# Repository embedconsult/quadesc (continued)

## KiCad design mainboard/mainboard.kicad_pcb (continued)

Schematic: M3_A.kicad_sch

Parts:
C40, C95: 1nF; C_0201_0603Metric
C41: 10uF; C_1206_3216Metric
C42: 4.7nF; C_0402_1005Metric
C43: 10nF; C_0402_1005Metric
NT13, NT14: NetTie_2; NetTie-2_SMD_Pad0.2mm
R39: 33k; R_0402_1005Metric
R40: 3.3k; R_0201_0603Metric
R41: 2.21; R_0805_2012Metric
R42: 4.7; R_0402_1005Metric
R43: 1mOhm; RES_1L00x_BRN
U8: CSD88599Q5DC; DMM0022A

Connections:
+BATT: C41.1, C43.1, U8.27 (VIN); also elsewhere on the board
GND: NT14.2, R43.2; also elsewhere on the board
M3_BEMFA: C40.2, R39.1, R40.1; also elsewhere on the board
M3_GHA: R42.1; also elsewhere on the board
M3_GLA: U8.22 (GL); also elsewhere on the board
M3_LSA: C40.1, C41.2, C43.2, NT13.2, R40.2, R41.2, R43.1, U8.12 (PGND), U8.13 (PGND), U8.14 (PGND), U8.15 (PGND), U8.16 (PGND), U8.17 (PGND), U8.18 (PGND), U8.19 (PGND), U8.20 (PGND)
M3_PHASEA: C42.1, R39.2, U8.3 (VSW), U8.4 (VSW), U8.5 (VSW), U8.6 (VSW), U8.7 (VSW), U8.8 (VSW), U8.9 (VSW), U8.10 (VSW), U8.11 (VSW); also elsewhere on the board
M3_SHA: U8.2 (SH); also elsewhere on the board
M3_SNA: C95.2, NT14.1; also elsewhere on the board
M3_SPA: C95.1, NT13.1; also elsewhere on the board
unnamed: C42.2, R41.1
unnamed: R42.2, U8.1 (GH)

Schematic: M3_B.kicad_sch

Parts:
C44, C96: 1nF; C_0201_0603Metric
C45: 10uF; C_1206_3216Metric
C46: 4.7nF; C_0402_1005Metric
C47: 10nF; C_0402_1005Metric
NT15, NT16: NetTie_2; NetTie-2_SMD_Pad0.2mm
R44: 33k; R_0402_1005Metric
R45: 3.3k; R_0201_0603Metric
R46: 2.21; R_0805_2012Metric
R47: 4.7; R_0402_1005Metric
R48: 1mOhm; RES_1L00x_BRN
U9: CSD88599Q5DC; DMM0022A

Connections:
+BATT: C45.1, C47.1, U9.27 (VIN); also elsewhere on the board
GND: NT16.2, R48.2; also elsewhere on the board
M3_BEMFB: C44.2, R44.1, R45.1; also elsewhere on the board
M3_GHB: R47.1; also elsewhere on the board
M3_GLB: U9.22 (GL); also elsewhere on the board
M3_LSB: C44.1, C45.2, C47.2, NT15.2, R45.2, R46.2, R48.1, U9.12 (PGND), U9.13 (PGND), U9.14 (PGND), U9.15 (PGND), U9.16 (PGND), U9.17 (PGND), U9.18 (PGND), U9.19 (PGND), U9.20 (PGND)
M3_PHASEB: C46.1, R44.2, U9.3 (VSW), U9.4 (VSW), U9.5 (VSW), U9.6 (VSW), U9.7 (VSW), U9.8 (VSW), U9.9 (VSW), U9.10 (VSW), U9.11 (VSW); also elsewhere on the board
M3_SHB: U9.2 (SH); also elsewhere on the board
M3_SNB: C96.2, NT16.1; also elsewhere on the board
M3_SPB: C96.1, NT15.1; also elsewhere on the board
unnamed: C46.2, R46.1
unnamed: R47.2, U9.1 (GH)

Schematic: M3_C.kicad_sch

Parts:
C48, C97: 1nF; C_0201_0603Metric
C49: 10uF; C_1206_3216Metric
C50: 4.7nF; C_0402_1005Metric
C51: 10nF; C_0402_1005Metric
NT17, NT18: NetTie_2; NetTie-2_SMD_Pad0.2mm
R49: 33k; R_0402_1005Metric
R50: 3.3k; R_0201_0603Metric
R51: 2.21; R_0805_2012Metric
R52: 4.7; R_0402_1005Metric
R53: 1mOhm; RES_1L00x_BRN
U10: CSD88599Q5DC; DMM0022A

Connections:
+BATT: C49.1, C51.1, U10.27 (VIN); also elsewhere on the board
GND: NT18.2, R53.2; also elsewhere on the board
M3_BEMFC: C48.2, R49.1, R50.1; also elsewhere on the board
M3_GHC: R52.1; also elsewhere on the board
M3_GLC: U10.22 (GL); also elsewhere on the board
M3_LSC: C48.1, C49.2, C51.2, NT17.2, R50.2, R51.2, R53.1, U10.12 (PGND), U10.13 (PGND), U10.14 (PGND), U10.15 (PGND), U10.16 (PGND), U10.17 (PGND), U10.18 (PGND), U10.19 (PGND), U10.20 (PGND)
M3_PHASEC: C50.1, R49.2, U10.3 (VSW), U10.4 (VSW), U10.5 (VSW), U10.6 (VSW), U10.7 (VSW), U10.8 (VSW), U10.9 (VSW), U10.10 (VSW), U10.11 (VSW); also elsewhere on the board
M3_SHC: U10.2 (SH); also elsewhere on the board
M3_SNC: C97.2, NT18.1; also elsewhere on the board
M3_SPC: C97.1, NT17.1; also elsewhere on the board
unnamed: C50.2, R51.1
unnamed: R52.2, U10.1 (GH)

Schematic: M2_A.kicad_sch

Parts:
C52, C92: 1nF; C_0201_0603Metric
C53: 10uF; C_1206_3216Metric
C54: 4.7nF; C_0402_1005Metric
C55: 10nF; C_0402_1005Metric
NT7, NT8: NetTie_2; NetTie-2_SMD_Pad0.2mm
R54: 33k; R_0402_1005Metric
R55: 3.3k; R_0201_0603Metric
R56: 2.21; R_0805_2012Metric
R57: 4.7; R_0402_1005Metric
R58: 1mOhm; RES_1L00x_BRN
U11: CSD88599Q5DC; DMM0022A

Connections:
+BATT: C53.1, C55.1, U11.27 (VIN); also elsewhere on the board
GND: NT8.2, R58.2; also elsewhere on the board
M2_BEMFA: C52.2, R54.1, R55.1; also elsewhere on the board
M2_GHA: R57.1; also elsewhere on the board
M2_GLA: U11.22 (GL); also elsewhere on the board
M2_LSA: C52.1, C53.2, C55.2, NT7.2, R55.2, R56.2, R58.1, U11.12 (PGND), U11.13 (PGND), U11.14 (PGND), U11.15 (PGND), U11.16 (PGND), U11.17 (PGND), U11.18 (PGND), U11.19 (PGND), U11.20 (PGND)
M2_PHASEA: C54.1, R54.2, U11.3 (VSW), U11.4 (VSW), U11.5 (VSW), U11.6 (VSW), U11.7 (VSW), U11.8 (VSW), U11.9 (VSW), U11.10 (VSW), U11.11 (VSW); also elsewhere on the board
M2_SHA: U11.2 (SH); also elsewhere on the board
M2_SNA: C92.2, NT8.1; also elsewhere on the board
M2_SPA: C92.1, NT7.1; also elsewhere on the board
unnamed: C54.2, R56.1
unnamed: R57.2, U11.1 (GH)

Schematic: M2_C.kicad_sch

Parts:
C60, C94: 1nF; C_0201_0603Metric
C61: 10uF; C_1206_3216Metric
C62: 4.7nF; C_0402_1005Metric
C63: 10nF; C_0402_1005Metric
NT11, NT12: NetTie_2; NetTie-2_SMD_Pad0.2mm
R64: 33k; R_0402_1005Metric
R65: 3.3k; R_0201_0603Metric
R66: 2.21; R_0805_2012Metric
R67: 4.7; R_0402_1005Metric
R68: 1mOhm; RES_1L00x_BRN
U13: CSD88599Q5DC; DMM0022A

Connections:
+BATT: C61.1, C63.1, U13.27 (VIN); also elsewhere on the board
GND: NT12.2, R68.2; also elsewhere on the board
M2_BEMFC: C60.2, R64.1, R65.1; also elsewhere on the board
M2_GHC: R67.1; also elsewhere on the board
M2_GLC: U13.22 (GL); also elsewhere on the board
M2_LSC: C60.1, C61.2, C63.2, NT11.2, R65.2, R66.2, R68.1, U13.12 (PGND), U13.13 (PGND), U13.14 (PGND), U13.15 (PGND), U13.16 (PGND), U13.17 (PGND), U13.18 (PGND), U13.19 (PGND), U13.20 (PGND)
M2_PHASEC: C62.1, R64.2, U13.3 (VSW), U13.4 (VSW), U13.5 (VSW), U13.6 (VSW), U13.7 (VSW), U13.8 (VSW), U13.9 (VSW), U13.10 (VSW), U13.11 (VSW); also elsewhere on the board
M2_SHC: U13.2 (SH); also elsewhere on the board
M2_SNC: C94.2, NT12.1; also elsewhere on the board
M2_SPC: C94.1, NT11.1; also elsewhere on the board
unnamed: C62.2, R66.1
unnamed: R67.2, U13.1 (GH)

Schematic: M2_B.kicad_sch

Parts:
C56, C93: 1nF; C_0201_0603Metric
C57: 10uF; C_1206_3216Metric
C58: 4.7nF; C_0402_1005Metric
C59: 10nF; C_0402_1005Metric
NT9, NT10: NetTie_2; NetTie-2_SMD_Pad0.2mm
R59: 33k; R_0402_1005Metric
R60: 3.3k; R_0201_0603Metric
R61: 2.21; R_0805_2012Metric
R62: 4.7; R_0402_1005Metric
R63: 1mOhm; RES_1L00x_BRN
U12: CSD88599Q5DC; DMM0022A

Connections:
+BATT: C57.1, C59.1, U12.27 (VIN); also elsewhere on the board
GND: NT10.2, R63.2; also elsewhere on the board
M2_BEMFB: C56.2, R59.1, R60.1; also elsewhere on the board
M2_GHB: R62.1; also elsewhere on the board
M2_GLB: U12.22 (GL); also elsewhere on the board
M2_LSB: C56.1, C57.2, C59.2, NT9.2, R60.2, R61.2, R63.1, U12.12 (PGND), U12.13 (PGND), U12.14 (PGND), U12.15 (PGND), U12.16 (PGND), U12.17 (PGND), U12.18 (PGND), U12.19 (PGND), U12.20 (PGND)
M2_PHASEB: C58.1, R59.2, U12.3 (VSW), U12.4 (VSW), U12.5 (VSW), U12.6 (VSW), U12.7 (VSW), U12.8 (VSW), U12.9 (VSW), U12.10 (VSW), U12.11 (VSW); also elsewhere on the board
M2_SHB: U12.2 (SH); also elsewhere on the board
M2_SNB: C93.2, NT10.1; also elsewhere on the board
M2_SPB: C93.1, NT9.1; also elsewhere on the board
unnamed: C58.2, R61.1
unnamed: R62.2, U12.1 (GH)

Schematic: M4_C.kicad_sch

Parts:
C36, C100: 1nF; C_0201_0603Metric
C37: 10uF; C_1206_3216Metric
C38: 4.7nF; C_0402_1005Metric
C39: 10nF; C_0402_1005Metric
NT23, NT24: NetTie_2; NetTie-2_SMD_Pad0.2mm
R34: 33k; R_0402_1005Metric
R35: 3.3k; R_0201_0603Metric
R36: 2.21; R_0805_2012Metric
R37: 4.7; R_0402_1005Metric
R38: 1mOhm; RES_1L00x_BRN
U7: CSD88599Q5DC; DMM0022A

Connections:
+BATT: C37.1, C39.1, U7.27 (VIN); also elsewhere on the board
GND: NT24.2, R38.2; also elsewhere on the board
M4_BEMFC: C36.2, R34.1, R35.1; also elsewhere on the board
M4_GHC: R37.1; also elsewhere on the board
M4_GLC: U7.22 (GL); also elsewhere on the board
M4_LSC: C36.1, C37.2, C39.2, NT23.2, R35.2, R36.2, R38.1, U7.12 (PGND), U7.13 (PGND), U7.14 (PGND), U7.15 (PGND), U7.16 (PGND), U7.17 (PGND), U7.18 (PGND), U7.19 (PGND), U7.20 (PGND)
M4_PHASEC: C38.1, R34.2, U7.3 (VSW), U7.4 (VSW), U7.5 (VSW), U7.6 (VSW), U7.7 (VSW), U7.8 (VSW), U7.9 (VSW), U7.10 (VSW), U7.11 (VSW); also elsewhere on the board
M4_SHC: U7.2 (SH); also elsewhere on the board
M4_SNC: C100.2, NT24.1; also elsewhere on the board
M4_SPC: C100.1, NT23.1; also elsewhere on the board
unnamed: C38.2, R36.1
unnamed: R37.2, U7.1 (GH)

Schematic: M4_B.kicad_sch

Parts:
C32, C99: 1nF; C_0201_0603Metric
C33: 10uF; C_1206_3216Metric
C34: 4.7nF; C_0402_1005Metric
C35: 10nF; C_0402_1005Metric
NT21, NT22: NetTie_2; NetTie-2_SMD_Pad0.2mm
R29: 33k; R_0402_1005Metric
R30: 3.3k; R_0201_0603Metric
R31: 2.21; R_0805_2012Metric
R32: 4.7; R_0402_1005Metric
R33: 1mOhm; RES_1L00x_BRN
U6: CSD88599Q5DC; DMM0022A

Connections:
+BATT: C33.1, C35.1, U6.27 (VIN); also elsewhere on the board
GND: NT22.2, R33.2; also elsewhere on the board
M4_BEMFB: C32.2, R29.1, R30.1; also elsewhere on the board
M4_GHB: R32.1; also elsewhere on the board
M4_GLB: U6.22 (GL); also elsewhere on the board
M4_LSB: C32.1, C33.2, C35.2, NT21.2, R30.2, R31.2, R33.1, U6.12 (PGND), U6.13 (PGND), U6.14 (PGND), U6.15 (PGND), U6.16 (PGND), U6.17 (PGND), U6.18 (PGND), U6.19 (PGND), U6.20 (PGND)
M4_PHASEB: C34.1, R29.2, U6.3 (VSW), U6.4 (VSW), U6.5 (VSW), U6.6 (VSW), U6.7 (VSW), U6.8 (VSW), U6.9 (VSW), U6.10 (VSW), U6.11 (VSW); also elsewhere on the board
M4_SHB: U6.2 (SH); also elsewhere on the board
M4_SNB: C99.2, NT22.1; also elsewhere on the board
M4_SPB: C99.1, NT21.1; also elsewhere on the board
unnamed: C34.2, R31.1
unnamed: R32.2, U6.1 (GH)

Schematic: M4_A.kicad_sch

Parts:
C28, C98: 1nF; C_0201_0603Metric
C29: 10uF; C_1206_3216Metric
C30: 4.7nF; C_0402_1005Metric
C31: 10nF; C_0402_1005Metric
NT19, NT20: NetTie_2; NetTie-2_SMD_Pad0.2mm
R24: 33k; R_0402_1005Metric
R25: 3.3k; R_0201_0603Metric
R26: 2.21; R_0805_2012Metric
R27: 4.7; R_0402_1005Metric
R28: 1mOhm; RES_1L00x_BRN
U5: CSD88599Q5DC; DMM0022A

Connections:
+BATT: C29.1, C31.1, U5.27 (VIN); also elsewhere on the board
GND: NT20.2, R28.2; also elsewhere on the board
M4_BEMFA: C28.2, R24.1, R25.1; also elsewhere on the board
M4_GHA: R27.1; also elsewhere on the board
M4_GLA: U5.22 (GL); also elsewhere on the board
M4_LSA: C28.1, C29.2, C31.2, NT19.2, R25.2, R26.2, R28.1, U5.12 (PGND), U5.13 (PGND), U5.14 (PGND), U5.15 (PGND), U5.16 (PGND), U5.17 (PGND), U5.18 (PGND), U5.19 (PGND), U5.20 (PGND)
M4_PHASEA: C30.1, R24.2, U5.3 (VSW), U5.4 (VSW), U5.5 (VSW), U5.6 (VSW), U5.7 (VSW), U5.8 (VSW), U5.9 (VSW), U5.10 (VSW), U5.11 (VSW); also elsewhere on the board
M4_SHA: U5.2 (SH); also elsewhere on the board
M4_SNA: C98.2, NT20.1; also elsewhere on the board
M4_SPA: C98.1, NT19.1; also elsewhere on the board
unnamed: C30.2, R26.1
unnamed: R27.2, U5.1 (GH)

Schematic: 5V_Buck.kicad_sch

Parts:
C76, C77: 4.7uF; C_0805_2012Metric
C78: .1uF; C_0201_0603Metric
C79: 6.8nF; C_0201_0603Metric
C80: 39pF; C_0201_0603Metric
C81, C88: 22uF; C_1206_3216Metric
C82: 1uF; C_0402_1005Metric
D3: D; PMEG4030AEXEQX
L1: 10uH; INDPM4441X200N
R84: 162k; R_0201_0603Metric
R85: 10.5k; R_0201_0603Metric
R86: 2k; R_0201_0603Metric
R87: 13k; R_0201_0603Metric
U17: TPS54360BDDAR; U_DDA_TEX

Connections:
+BATT: C76.1, C77.1, U17.2 (VIN); also elsewhere on the board
BUCK_OUT: C81.1, C82.1, C88.1, L1.2, R85.2; also elsewhere on the board
GND: C76.2, C77.2, C79.2, C80.2, C81.2, C82.2, C88.2, D3.2 (A), R84.2, R86.2, U17.7 (GND), U17.9 (EPAD); also elsewhere on the board
unnamed: C79.1, R87.1
unnamed: C78.2, D3.1 (K), L1.1, U17.8 (SW)
unnamed: C78.1, U17.1 (BOOT)
unnamed: C80.1, R87.2, U17.6 (COMP)
unnamed: R85.1, R86.1, U17.5 (FB)
unnamed: R84.1, U17.4 (RT/CLK)

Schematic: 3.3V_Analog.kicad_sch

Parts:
C83: 10uF; C_0805_2012Metric
C84: .1uF; C_0201_0603Metric
C85: 1uF; C_0402_1005Metric
C86, C87: 22uF; C_1206_3216Metric
R88, R89, R90: 0; R_0201_0603Metric
U18: TPS7A4701RGWR; RGW0020A-IPC_A

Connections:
BUCK_OUT: C83.1, C84.1, U18.13 (EN), U18.15 (IN), U18.16 (IN); also elsewhere on the board
GND: C83.2, C84.2, C85.2, C86.2, C87.2, R88.2, R89.2, R90.2, U18.7 (GND), U18.21 (Thermal_Pad); also elsewhere on the board
unnamed: R88.1, U18.12 (0P1V)
unnamed: R89.1, U18.11 (0P2V)
unnamed: R90.1, U18.8 (1P6V)
unnamed: C85.1, U18.14 (NR)
VAA: C86.1, C87.1, U18.1 (OUT), U18.3 (SENSE_FB), U18.20 (OUT); also elsewhere on the board

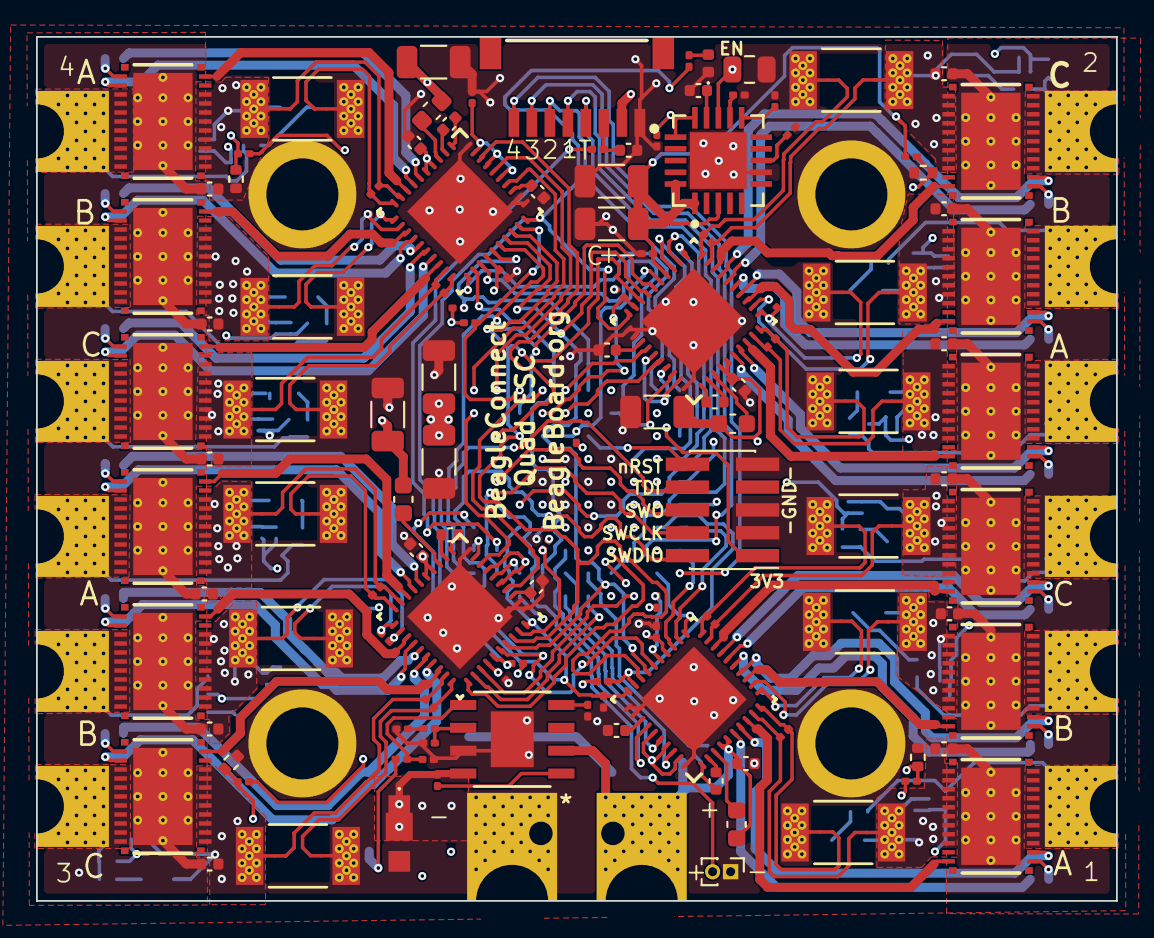
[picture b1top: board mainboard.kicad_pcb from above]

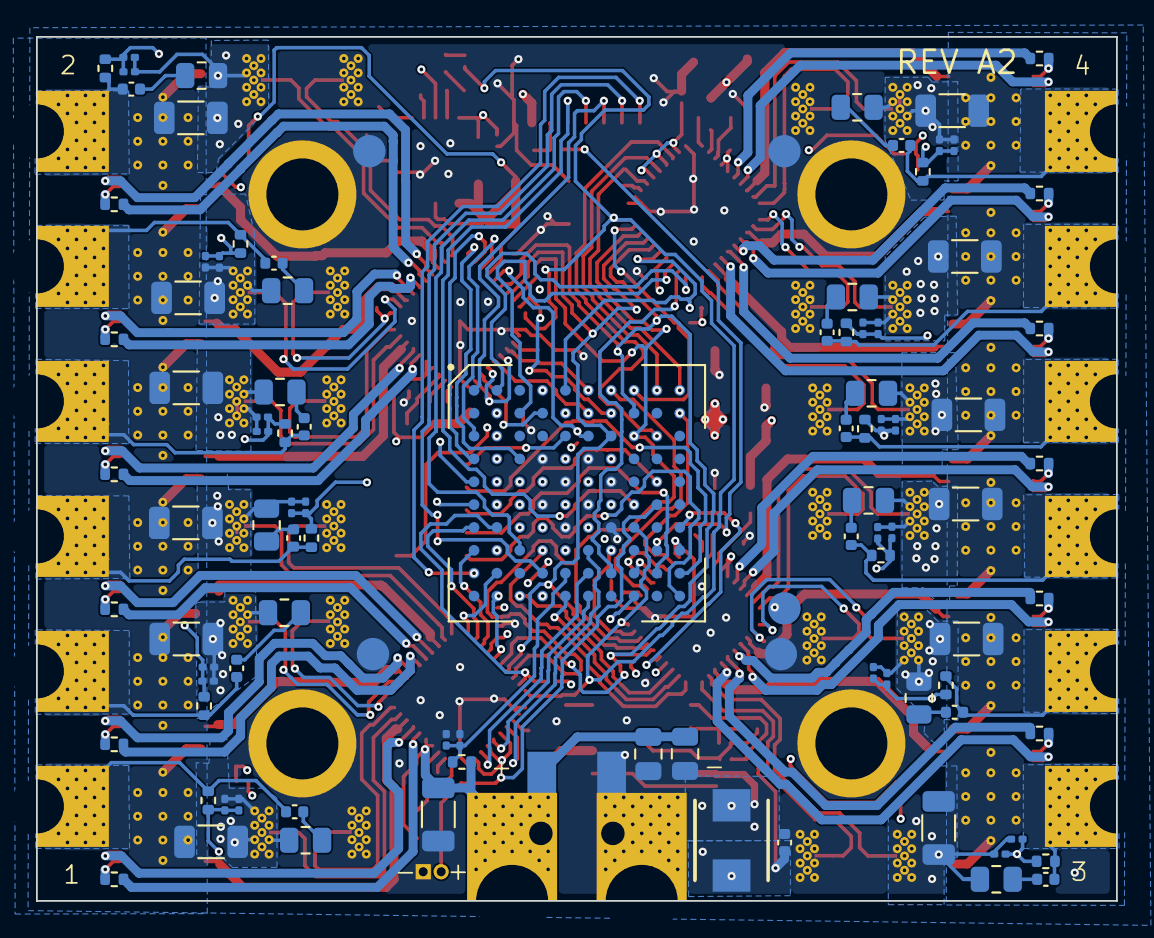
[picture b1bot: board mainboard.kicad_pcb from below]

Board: 6 copper layers, 60.0 x 48.0 mm, 247 parts (95 on the bottom side), 207 nets.

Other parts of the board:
MH1, MH2, MH3, MH4: MountingHole_M3_3.0mmDrill_6.0mmPad

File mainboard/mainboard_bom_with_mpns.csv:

Reference,Qty,Value,MPN,Cap Dielectric,Cap Voltage Rating,DNP,Footprint,Datasheet
C1,1,1000uF,TBD,Aluminum electrolytic,35v,DNP,,
"C2,C8,C14,C20",4,10uF,C1210C106K5RACTU,X7R,50V,,Capacitor_SMD:C_1210_3225Metric,
"C3,C9,C15,C21,C27,C78,C84",7,.1uF,CC0201KRX7R6BB104,X7R,10V,,Capacitor_SMD:C_0201_0603Metric,
"C4,C10,C16,C22,C26,C82,C85",7,1uF,CC0402KRX7R6BB105,X7R,10V,,Capacitor_SMD:C_0402_1005Metric,
"C5,C11,C17,C23",4,.1uF,CC0402KRX7R9BB104,X7R,50V,,Capacitor_SMD:C_0402_1005Metric,
"C6,C12,C18,C24",4,1uF,C0603C105K3RACTU,X7R,25V,,Capacitor_SMD:C_0603_1608Metric,
"C7,C13,C19,C25",4,47nF,CC0402KRX7R9BB473,X7R,50V,,Capacitor_SMD:C_0402_1005Metric,
"C28,C32,C36,C40,C44,C48,C52,C56,C60,C64,C68,C72",12,1nF,GRM0335C1H102JE01D,C0G/NP0,50V,,Capacitor_SMD:C_0201_0603Metric,
"C29,C33,C37,C41,C45,C49,C53,C57,C61,C65,C69,C73",12,2.2uF,C2012X7R1H225K125AC,X7R,50V,,Capacitor_SMD:C_0805_2012Metric,
"C30,C34,C38,C42,C46,C50,C54,C58,C62,C66,C70,C74",12,4.7nF,CC0402KRX7R0BB472,X7R,100V,,Capacitor_SMD:C_0402_1005Metric,
"C31,C35,C39,C43,C47,C51,C55,C59,C63,C67,C71,C75",12,10nF,CC0402KRX7R0BB103,X7R,100V,,Capacitor_SMD:C_0402_1005Metric,
"C76,C77",2,4.7uF,C2012X7R1H475K125AC,X7R,50V,,Capacitor_SMD:C_0805_2012Metric,
C79,1,6.8nF,CC0201KRX7R7BB682,X7R,16V,,Capacitor_SMD:C_0201_0603Metric,
C80,1,39pF,CC0201JRNPO9BN390,C0G (NP0),50V,,Capacitor_SMD:C_0201_0603Metric,
"C81,C86,C87, C88",4,22uF,CC1206MKX7R7BB226,X7R,16V,,Capacitor_SMD:C_1206_3216Metric,
C83,1,10uF,C2012X7R1A106K125AC,X7R,10V,,Capacitor_SMD:C_0805_2012Metric,
D1,1,D,SMAJ26A,,,,SMAJ26A:SMAJ26A,
D2,1,LED,APHHS1005LZGCK-V,,,,LED_SMD:LED_0402_1005Metric,https://www.kingbrightusa.com/product.asp?catalog_name=LED&p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
D3,1,D,PMEG6030AEXE-QX,,,,PMEG6030AEXE-QX:PMEG4030AEXEQX,
J1,1,,N/A - PCB wire pad,,,,WirePad_Battery_2P_5.0x9.0_DualSide:WirePad_Battery_2P_5.0x9.0_DualSide,
"J2,J3,J4,J5",4,,N/A - PCB wire pad,,,,WirePad_Motor_3P_4.0x6.0_DualSide:WirePad_Motor_3P_4.0x6.0_DualSide,
J6,1,Conn_01x08_Pin,SM08B-SRSS-TB(LF)(SN),,,,SM08B_SRSS_TB_new:JST_SM08B-SRSS-TB,
J7,1,ARM/JTAG,DNP,,,DNP,,
J8,1,MikroBUS L,DNP,,,DNP,,
J10,1,MikroBUS R,DNP,,,DNP,,
L1,1,10uH,SRP4020T-100M,,,,SRP4020T-100M:INDPM4441X200N,
"R1,R3,R4,R6,R7,R8,R10,R12,R20,R22. R2,R5,R9,R11",14,10k,RC0201FR-0710KL,,,,Resistor_SMD:R_0201_0603Metric,
"R13,R14,R15,R16,R17",5,0,RC0402JR-070RL,,,,Resistor_SMD:R_0402_1005Metric,
"R18,R23",2,2.2k,RC0201FR-072K2L,,,,Resistor_SMD:R_0201_0603Metric,
R19,1,100k,RC0402FR-07100KL,,,,Resistor_SMD:R_0402_1005Metric,
R21,1,4.7k,RC0201FR-074K7L,,,,Resistor_SMD:R_0201_0603Metric,
"R24,R29,R34,R39,R44,R49,R54,R59,R64,R69,R74,R79",12,33k,RC0402FR-0733KL,,,,Resistor_SMD:R_0402_1005Metric,
"R25,R30,R35,R40,R45,R50,R55,R60,R65,R70,R75,R80",12,3.3k,RC0201FR-073K3L,,,,Resistor_SMD:R_0201_0603Metric,
"R26,R31,R36,R41,R46,R51,R56,R61,R66,R71,R76,R81",12,2.21,CRCW08052R21FKEAHP,,,,Resistor_SMD:R_0805_2012Metric,
"R27,R32,R37,R42,R47,R52,R57,R62,R67,R72,R77,R82",12,4.7,RC0402FR-074R7L,,,,Resistor_SMD:R_0402_1005Metric,
"R28,R33,R38,R43,R48,R53,R58,R63,R68,R73,R78,R83",12,1mOhm,CSS2H-2512R-1L00F,,,,CSS2H-2512R-1L00F_new:RES_1L00x_BRN,
R84,1,162k,RC0201FR-07162KL,,,,Resistor_SMD:R_0201_0603Metric,
R85,1,10.5k,RC0201FR-0710K5L,,,,Resistor_SMD:R_0201_0603Metric,
R86,1,2k,RC0201FR-072KL,,,,Resistor_SMD:R_0201_0603Metric,
R87,1,13k,RC0201FR-0713KL,,,,Resistor_SMD:R_0201_0603Metric,
"R88,R89,R90",3,0,RC0201JR-070RL,,,,Resistor_SMD:R_0201_0603Metric,
"TH1,TH2,TH3,TH4",4,Thermistor_NTC,NCU15XH103F60RC,,,,Resistor_SMD:R_0402_1005Metric,
"U1,U2,U3,U4",4,DRV8323RSRGZT,DRV8323RSRGZT,,,,DRV8323RSRGZT_new:RGZ0048A,https://www.ti.com/lit/gpn/drv8323r
"U5,U6,U7,U8,U9,U10,U11,U12,U13,U14,U15,U16",12,CSD88599Q5DC,CSD88599Q5DC,,,,CSD88599Q5DC:DMM0022A,https://www.ti.com/lit/gpn/csd88599q5dc
U17,1,TPS54360BDDAR,TPS54360BDDAR,,,,TPS54360BDDAR_new:U_DDA_TEX,https://www.ti.com/lit/gpn/tps54360b
U18,1,TPS7A4701RGWR,TPS7A4701RGWR,,,,TPS7A4701RGWR_new:RGW0020A-MFG,https://www.ti.com/lit/gpn/tps7a47

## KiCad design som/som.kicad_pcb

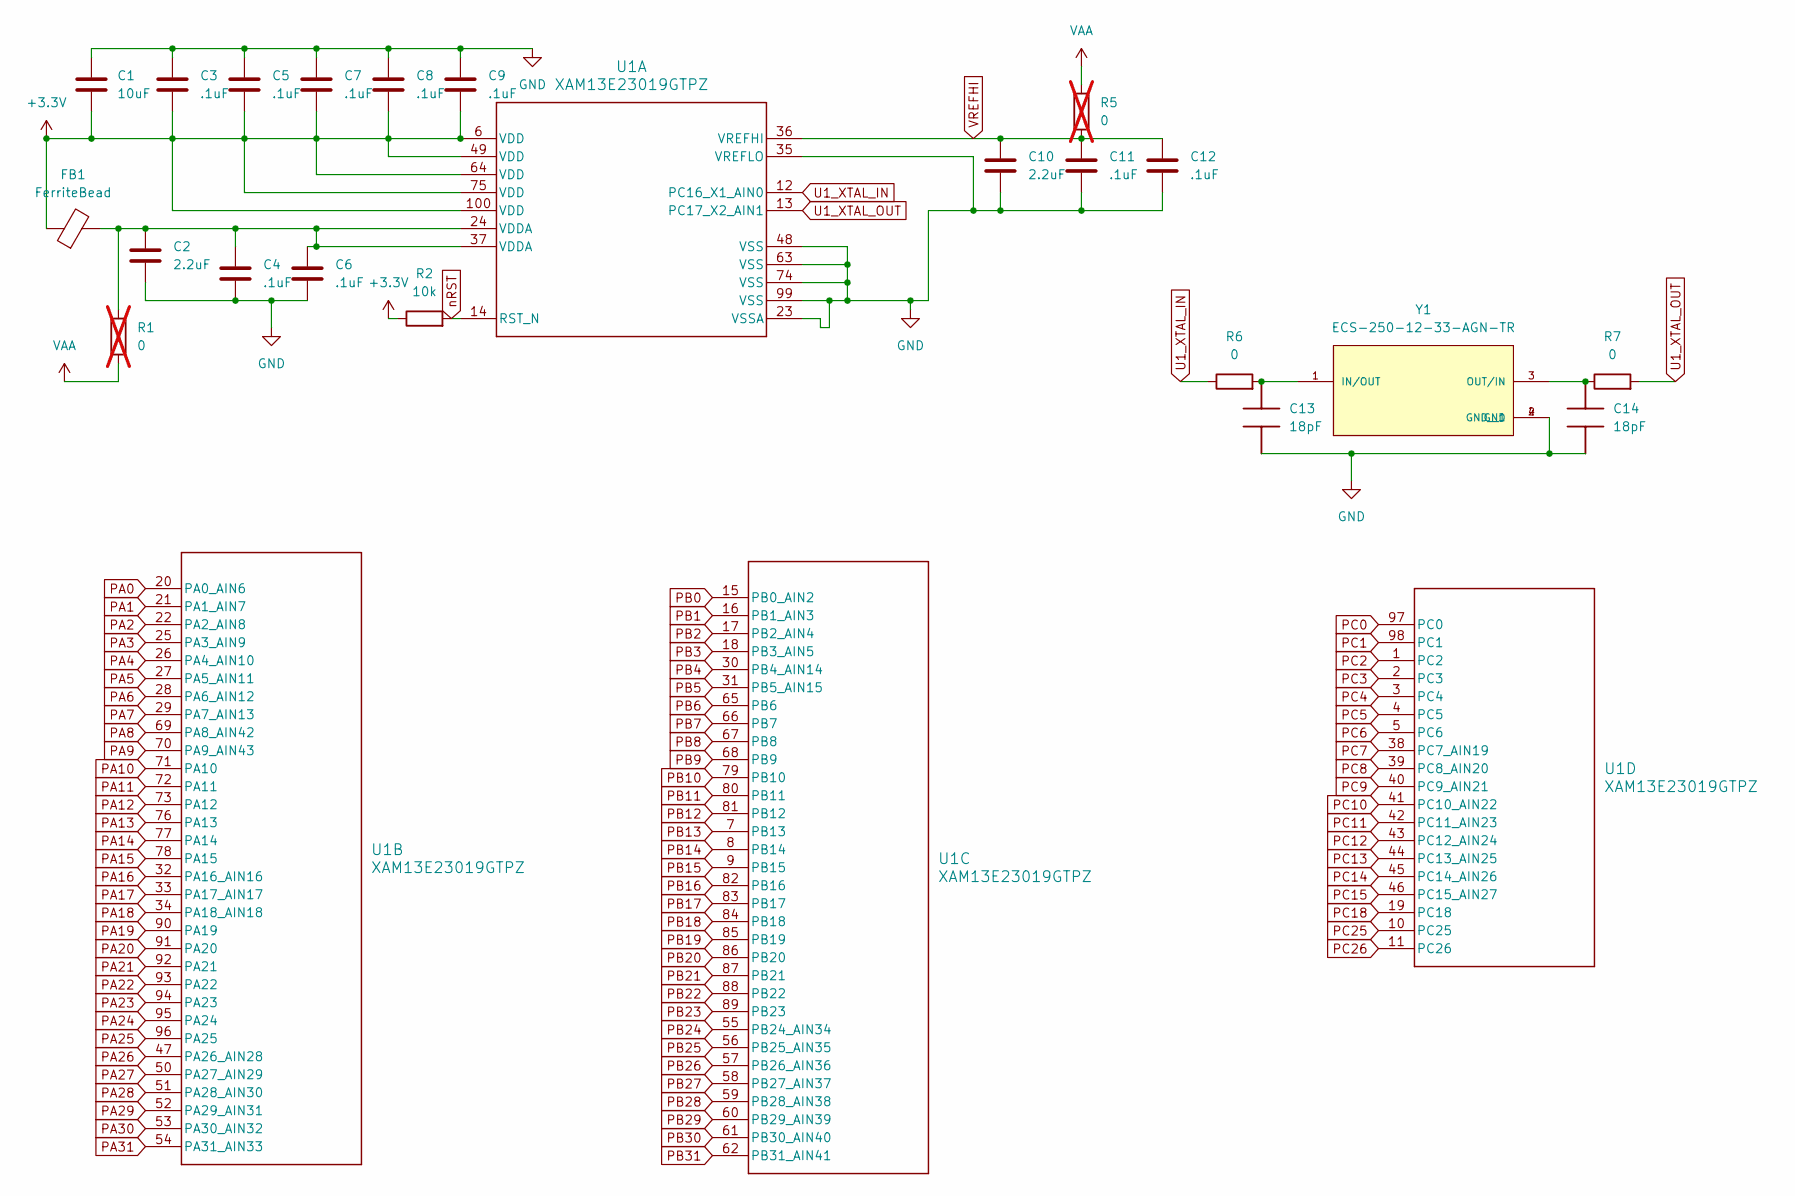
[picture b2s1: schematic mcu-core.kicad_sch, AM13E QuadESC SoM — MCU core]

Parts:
C1: 10uF; C_0603_1608Metric
C2, C10: 2.2uF; C_0402_1005Metric
C3, C4, C5, C6, C7, C8, C9, C11, C12: .1uF; C_0201_0603Metric
C13, C14: 18pF; C_0402_1005Metric
FB1: FerriteBead; L_0603_1608Metric
R1, R5: 0; R_0201_0603Metric; not fitted
R2: 10k; R_0201_0603Metric
R6, R7: 0; R_0201_0603Metric
U1: XAM13E23019GTPZ; PZ0100A-MFG
Y1: ECS-250-12-33-AGN-TR; XTAL_ECS-250-12-33-AGN-TR

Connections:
+3.3V: C1.2, C3.1, C5.1, C7.1, C8.1, C9.1, FB1.1, R2.1, U1.6 (VDD), U1.49 (VDD), U1.64 (VDD), U1.75 (VDD), U1.100 (VDD); also elsewhere on the board
AN: U1.51 (PA28_AIN30); also elsewhere on the board
BSL_I2C_SCL: U1.94 (PA23); also elsewhere on the board
BSL_I2C_SDA: U1.93 (PA22); also elsewhere on the board
BSL_INVOKE: U1.28 (PA6_AIN12); also elsewhere on the board
BSL_UART_RX: U1.21 (PA1_AIN7); also elsewhere on the board
BSL_UART_TX: U1.20 (PA0_AIN6); also elsewhere on the board
CAN_RX: U1.72 (PA11); also elsewhere on the board
CAN_TERM: U1.97 (PC0); also elsewhere on the board
CAN_TX: U1.73 (PA12); also elsewhere on the board
GND: C1.1, C2.2, C3.2, C4.1, C5.2, C6.1, C7.2, C8.2, C9.2, C10.2, C11.1, C12.1, C13.1, C14.1, U1.23 (VSSA), U1.35 (VREFLO), U1.48 (VSS), U1.63 (VSS), U1.74 (VSS), U1.99 (VSS), Y1.2 (GND), Y1.4 (GND__1); also elsewhere on the board
INT: U1.17 (PB2_AIN4); also elsewhere on the board
unnamed: C2.1, C4.2, C6.2, FB1.2, R1.1, U1.24 (VDDA), U1.37 (VDDA)
unnamed: C13.2, R6.2, Y1.1 (IN/OUT)
unnamed: C14.2, R7.1, Y1.3 (OUT/IN)
PA2: U1.22 (PA2_AIN8); also elsewhere on the board
PA3: U1.25 (PA3_AIN9); also elsewhere on the board
PA4: U1.26 (PA4_AIN10); also elsewhere on the board
PA5: U1.27 (PA5_AIN11); also elsewhere on the board
PA7: U1.29 (PA7_AIN13); also elsewhere on the board
PA8: U1.69 (PA8_AIN42); also elsewhere on the board
PA9: U1.70 (PA9_AIN43); also elsewhere on the board
PA10: U1.71 (PA10); also elsewhere on the board
PA13: U1.76 (PA13); also elsewhere on the board
PA14: U1.77 (PA14); also elsewhere on the board
PA15: U1.78 (PA15); also elsewhere on the board
PA16: U1.32 (PA16_AIN16); also elsewhere on the board
PA17: U1.33 (PA17_AIN17); also elsewhere on the board
PA18: U1.34 (PA18_AIN18); also elsewhere on the board
PA19: U1.90 (PA19); also elsewhere on the board
PA20: U1.91 (PA20); also elsewhere on the board
PA21: U1.92 (PA21); also elsewhere on the board
PA24: U1.95 (PA24); also elsewhere on the board
PA25: U1.96 (PA25); also elsewhere on the board
PA26: U1.47 (PA26_AIN28); also elsewhere on the board
PA27: U1.50 (PA27_AIN29); also elsewhere on the board
PA29: U1.52 (PA29_AIN31); also elsewhere on the board
PA30: U1.53 (PA30_AIN32); also elsewhere on the board
PA31: U1.54 (PA31_AIN33); also elsewhere on the board
PB0: U1.15 (PB0_AIN2); also elsewhere on the board
PB1: U1.16 (PB1_AIN3); also elsewhere on the board
PB3: U1.18 (PB3_AIN5); also elsewhere on the board
PB4: U1.30 (PB4_AIN14); also elsewhere on the board
PB5: U1.31 (PB5_AIN15); also elsewhere on the board
PB6: U1.65 (PB6); also elsewhere on the board
PB7: U1.66 (PB7); also elsewhere on the board
PB8: U1.67 (PB8); also elsewhere on the board
PB9: U1.68 (PB9); also elsewhere on the board
PB10: U1.79 (PB10); also elsewhere on the board
PB11: U1.80 (PB11); also elsewhere on the board
PB12: U1.81 (PB12); also elsewhere on the board
PB13: U1.7 (PB13); also elsewhere on the board
PB14: U1.8 (PB14); also elsewhere on the board
PB15: U1.9 (PB15); also elsewhere on the board
PB16: U1.82 (PB16); also elsewhere on the board
PB17: U1.83 (PB17); also elsewhere on the board
PB18: U1.84 (PB18); also elsewhere on the board
PB19: U1.85 (PB19); also elsewhere on the board
PB20: U1.86 (PB20); also elsewhere on the board
PB21: U1.87 (PB21); also elsewhere on the board
PB22: U1.88 (PB22); also elsewhere on the board
PB23: U1.89 (PB23); also elsewhere on the board
PB24: U1.55 (PB24_AIN34); also elsewhere on the board
PB25: U1.56 (PB25_AIN35); also elsewhere on the board
PB26: U1.57 (PB26_AIN36); also elsewhere on the board
PB27: U1.58 (PB27_AIN37); also elsewhere on the board
PB28: U1.59 (PB28_AIN38); also elsewhere on the board
PB29: U1.60 (PB29_AIN39); also elsewhere on the board
PB30: U1.61 (PB30_AIN40); also elsewhere on the board
PB31: U1.62 (PB31_AIN41); also elsewhere on the board
PC1: U1.98 (PC1); also elsewhere on the board
PC2: U1.1 (PC2); also elsewhere on the board
PC3: U1.2 (PC3); also elsewhere on the board
PC4: U1.3 (PC4); also elsewhere on the board
PC5: U1.4 (PC5); also elsewhere on the board
PC6: U1.5 (PC6); also elsewhere on the board
PC7: U1.38 (PC7_AIN19); also elsewhere on the board
PC8: U1.39 (PC8_AIN20); also elsewhere on the board
PC9: U1.40 (PC9_AIN21); also elsewhere on the board
PC10: U1.41 (PC10_AIN22); also elsewhere on the board
PC11: U1.42 (PC11_AIN23); also elsewhere on the board
PC12: U1.43 (PC12_AIN24); also elsewhere on the board
PC13: U1.44 (PC13_AIN25); also elsewhere on the board
PC14: U1.45 (PC14_AIN26); also elsewhere on the board
PC15: U1.46 (PC15_AIN27); also elsewhere on the board
PC18: U1.19 (PC18); also elsewhere on the board
PC25: U1.10 (PC25); also elsewhere on the board
PC26: U1.11 (PC26); also elsewhere on the board
U1_XTAL_IN: R6.1, U1.12 (PC16_X1_AIN0)
U1_XTAL_OUT: R7.2, U1.13 (PC17_X2_AIN1)
VAA: R1.2, R5.1; also elsewhere on the board
VREFHI: C10.1, C11.2, C12.2, R5.2, U1.36 (VREFHI)
nRST: R2.2, U1.14 (RST_N); also elsewhere on the board

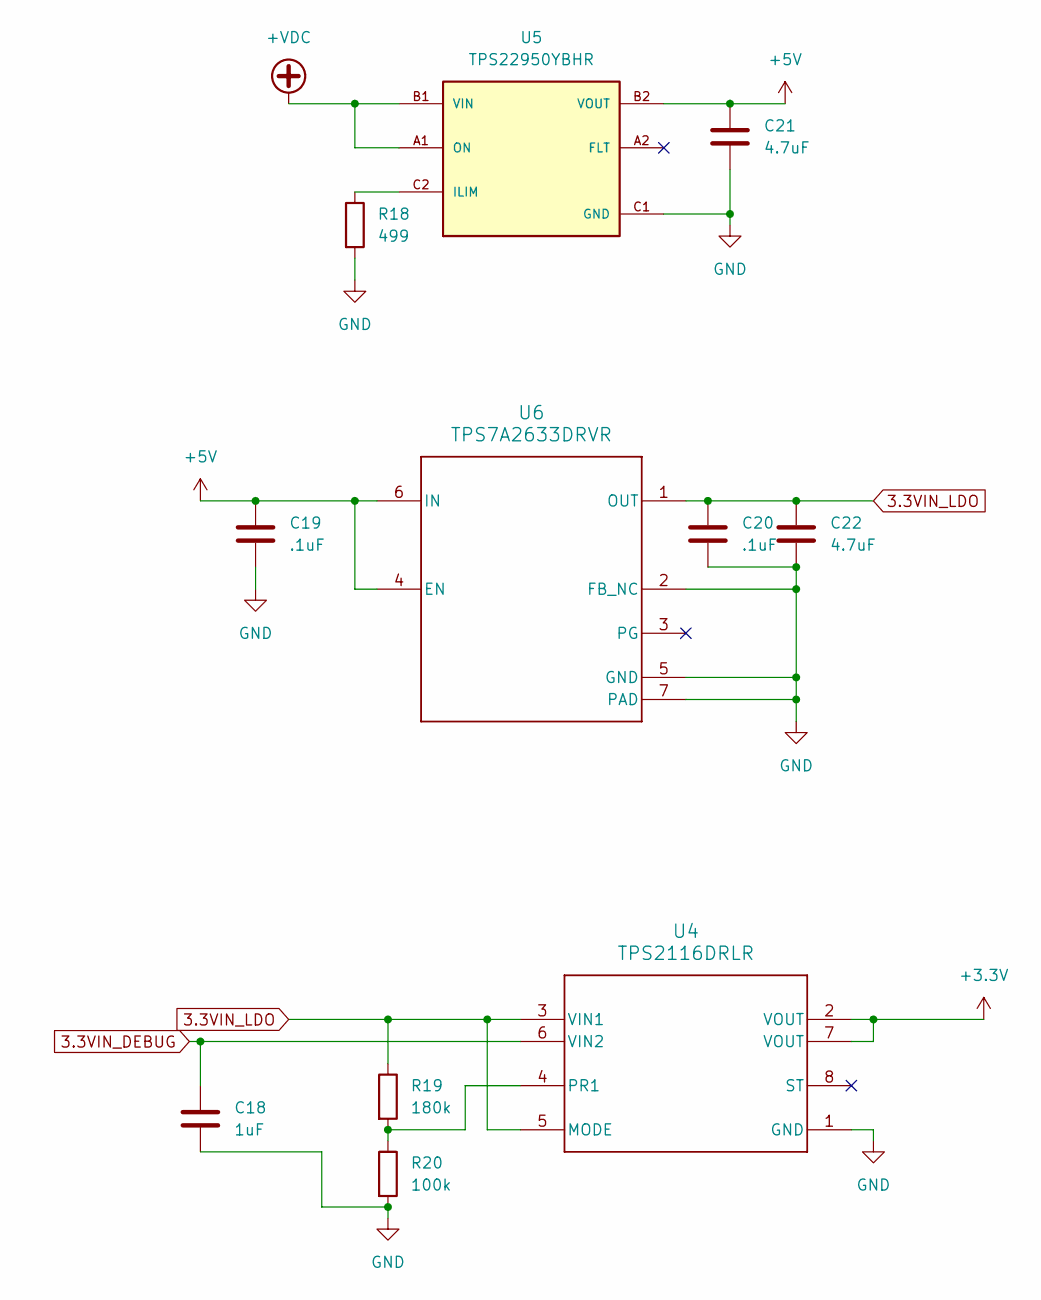
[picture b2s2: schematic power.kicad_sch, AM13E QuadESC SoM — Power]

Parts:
C18: 1uF; C_0402_1005Metric
C19, C20: .1uF; C_0201_0603Metric
C21, C22: 4.7uF; C_0402_1005Metric
R18: 499; R_0201_0603Metric
R19: 180k; R_0201_0603Metric
R20: 100k; R_0201_0603Metric
U4: TPS2116DRLR; DRL0008A-MFG
U5: TPS22950YBHR; IC_TPS22950YBHR; PARTREV December 2020
U6: TPS7A2633DRVR; DRV0006A

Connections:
3.3VIN_DEBUG: C18.1, U4.6 (VIN2); also elsewhere on the board
3.3VIN_LDO: C20.1, C22.1, R19.1, U4.3 (VIN1), U4.5 (MODE), U6.1 (OUT)
+3.3V: U4.2 (VOUT), U4.7 (VOUT); also elsewhere on the board
+5V: C19.1, C21.1, U5.B2 (VOUT), U6.4 (EN), U6.6 (IN); also elsewhere on the board
+VDC: U5.A1 (ON), U5.B1 (VIN); also elsewhere on the board
GND: C18.2, C19.2, C20.2, C21.2, C22.2, R18.2, R20.2, U4.1 (GND), U5.C1 (GND), U6.2 (FB_NC), U6.5 (GND), U6.7 (PAD); also elsewhere on the board
unnamed: R19.2, R20.1, U4.4 (PR1)
unnamed: R18.1, U5.C2 (ILIM)

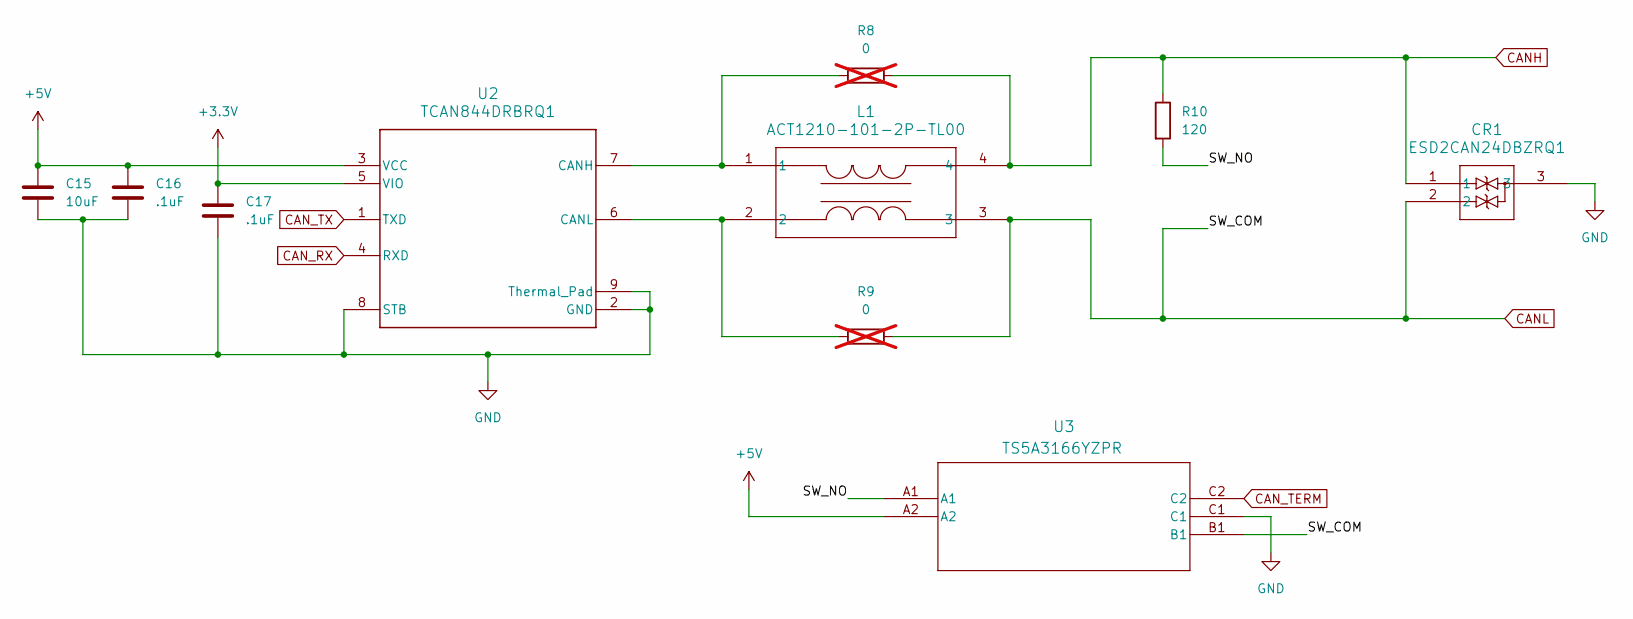
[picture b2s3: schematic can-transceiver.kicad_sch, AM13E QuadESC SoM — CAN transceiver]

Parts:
C15: 10uF; C_0603_1608Metric
C16, C17: .1uF; C_0201_0603Metric
CR1: ESD2CAN24DBZRQ1; SOT-23_DBZ_TEX
L1: ACT1210-101-2P-TL00; IND_01-2P-TL00_TDK
R8, R9: 0; R_0201_0603Metric; not fitted
R10: 120; R_1206_3216Metric
U2: TCAN844DRBRQ1; DRB0008J-MFG
U3: TS5A3166YZPR; YZP5

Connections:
+3.3V: C17.1, U2.5 (VIO); also elsewhere on the board
+5V: C15.1, C16.1, U2.3 (VCC), U3.A2; also elsewhere on the board
/can-transceiver/SW_NO: R10.2, U3.A1
CANH: CR1.1, L1.4, R8.2, R10.1; also elsewhere on the board
CANL: CR1.2, L1.3, R9.1, U3.B1; also elsewhere on the board
CAN_RX: U2.4 (RXD); also elsewhere on the board
CAN_TERM: U3.C2; also elsewhere on the board
CAN_TX: U2.1 (TXD); also elsewhere on the board
GND: C15.2, C16.2, C17.2, CR1.3, U2.2 (GND), U2.8 (STB), U2.9 (Thermal_Pad), U3.C1; also elsewhere on the board
unnamed: L1.1, R8.1, U2.7 (CANH)
unnamed: L1.2, R9.2, U2.6 (CANL)
